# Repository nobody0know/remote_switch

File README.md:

# remote_switch

深技大宿舍
因为太懒，懒得下床关灯所以整了这货

细则：

使用esp32 DevKitC V4开发板和ESP-IDF加上巴法云的物联网服务器进行开发

使用请参考ESP-IDF文档安装ESP-IDF的组件，并注册巴法云账号，于MQTT设备云中建立

lightleft002，lightright002，lightall002三个主题尾缀002是用于小程序将其识别为灯并展示在小程序中以便快捷使用，前缀可任意改

我在程序中加入了OTA空中升级功能，在控制台对lightall002这个主题发送updata即可自动从此主题的OTA服务器中下载新版本固件进行升级，若没有更新版本则就算进入OTA也不会触发升级，可在config SDK 那更新固件版本后编译上传bin文件再次升级即可

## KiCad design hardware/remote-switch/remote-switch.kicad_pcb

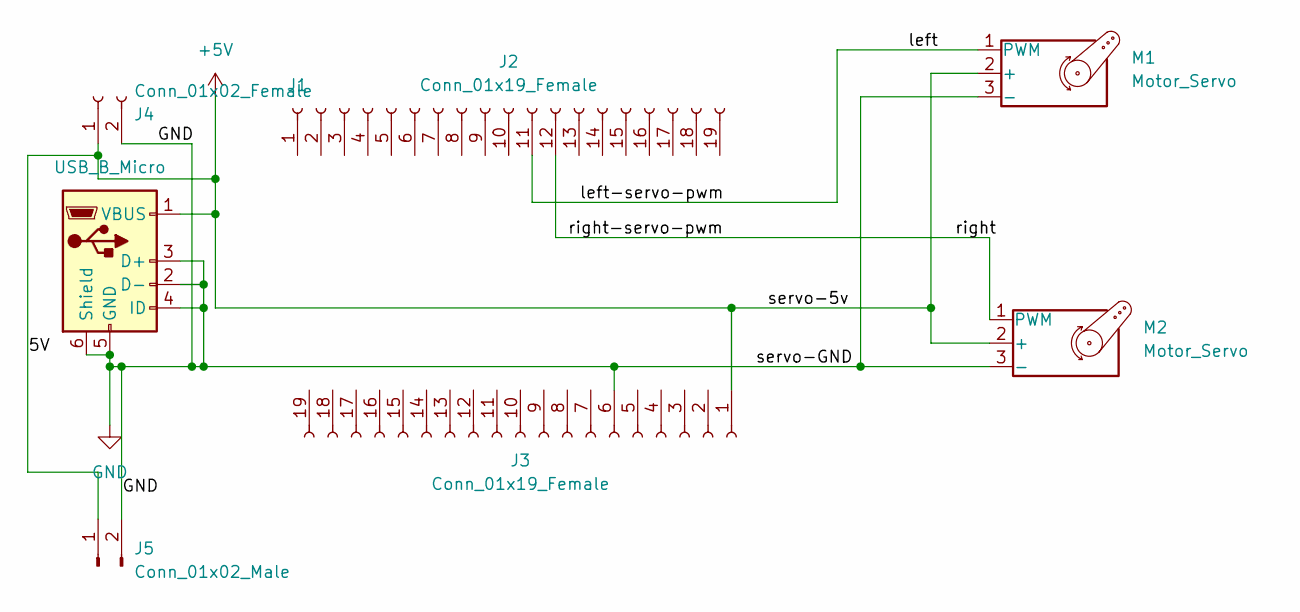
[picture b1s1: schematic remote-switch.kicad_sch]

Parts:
J1: USB_B_Micro; USB_Micro-B_Molex-105017-0001
J2, J3: Conn_01x19_Female; PinSocket_1x19_P2.54mm_Vertical
J4: Conn_01x02_Female; PinHeader_1x02_P2.54mm_Horizontal
J5: Conn_01x02_Male; PinHeader_1x02_P2.54mm_Horizontal
M1, M2: Motor_Servo; PinHeader_1x03_P2.54mm_Horizontal

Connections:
+5V: J1.1 (VBUS), J3.1, J4.1, J5.1, M1.2 (+), M2.2 (+)
/left: J2.11, M1.1 (PWM)
/right: J2.12, M2.1 (PWM)
GND: J1.2 (D-), J1.3 (D+), J1.4 (ID), J1.5 (GND), J1.6 (Shield), J3.6, J4.2, J5.2, M1.3 (-), M2.3 (-)

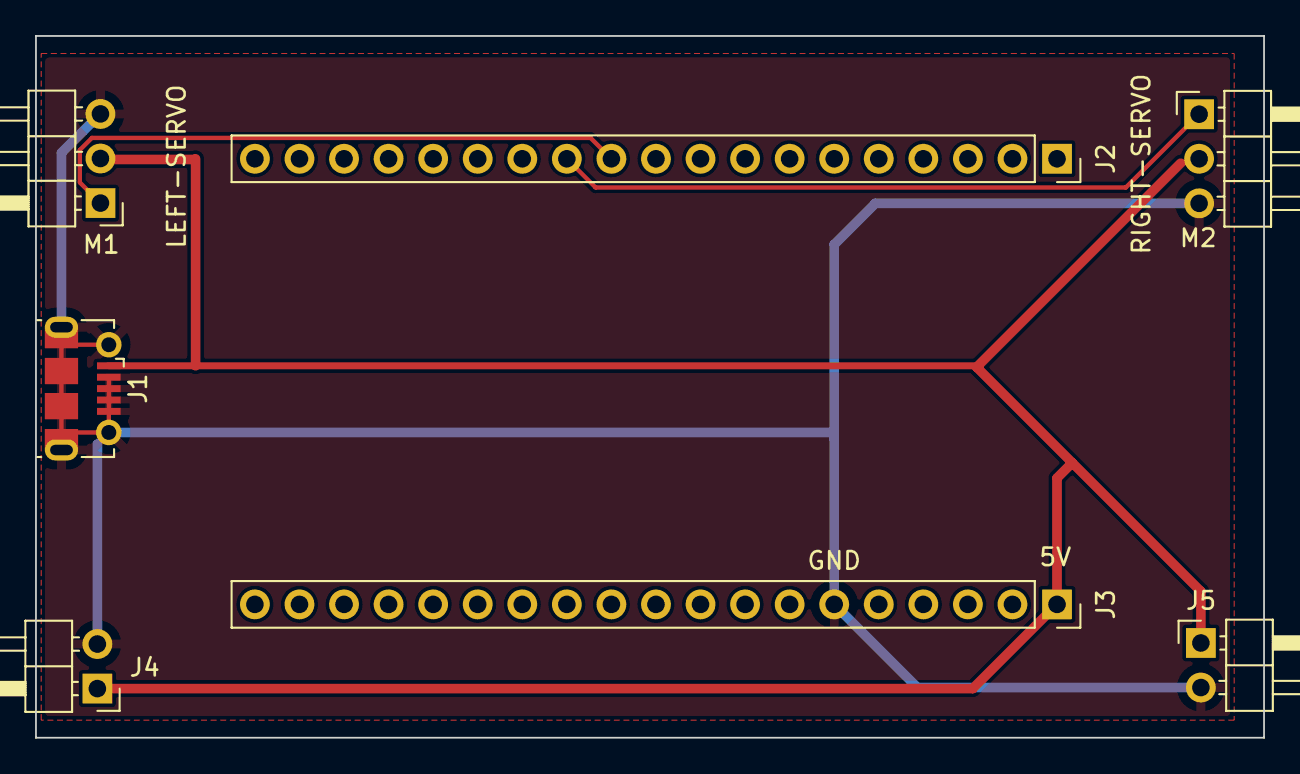
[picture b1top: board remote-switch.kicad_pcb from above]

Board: 2 copper layers, 70.0 x 40.0 mm, 7 parts (0 on the bottom side), 4 nets.

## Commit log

2022-07-19 first
2022-07-20 2022 7 20 控制函数完成
2022-07-20 解决数据传递bug
2022-08-09 真正的搞完了，修改了topic使其能被小程序识别为灯
2022-08-10 增加gitignore
2022-08-11 添加OTA远程升级功能
2022-08-11 开发板底板和开关外结构上传
2022-08-14 添加部分关键注释
2022-08-14 readme更新
2022-08-21 添加红外控制部分
    软件上跑通了
2022-08-21 修改对小程序的支持
2024-11-22 修改当年屎山的无用电机控制代码，修改代码至IDF V5.3.0能够通过编译
    仅供参考，不包好用
